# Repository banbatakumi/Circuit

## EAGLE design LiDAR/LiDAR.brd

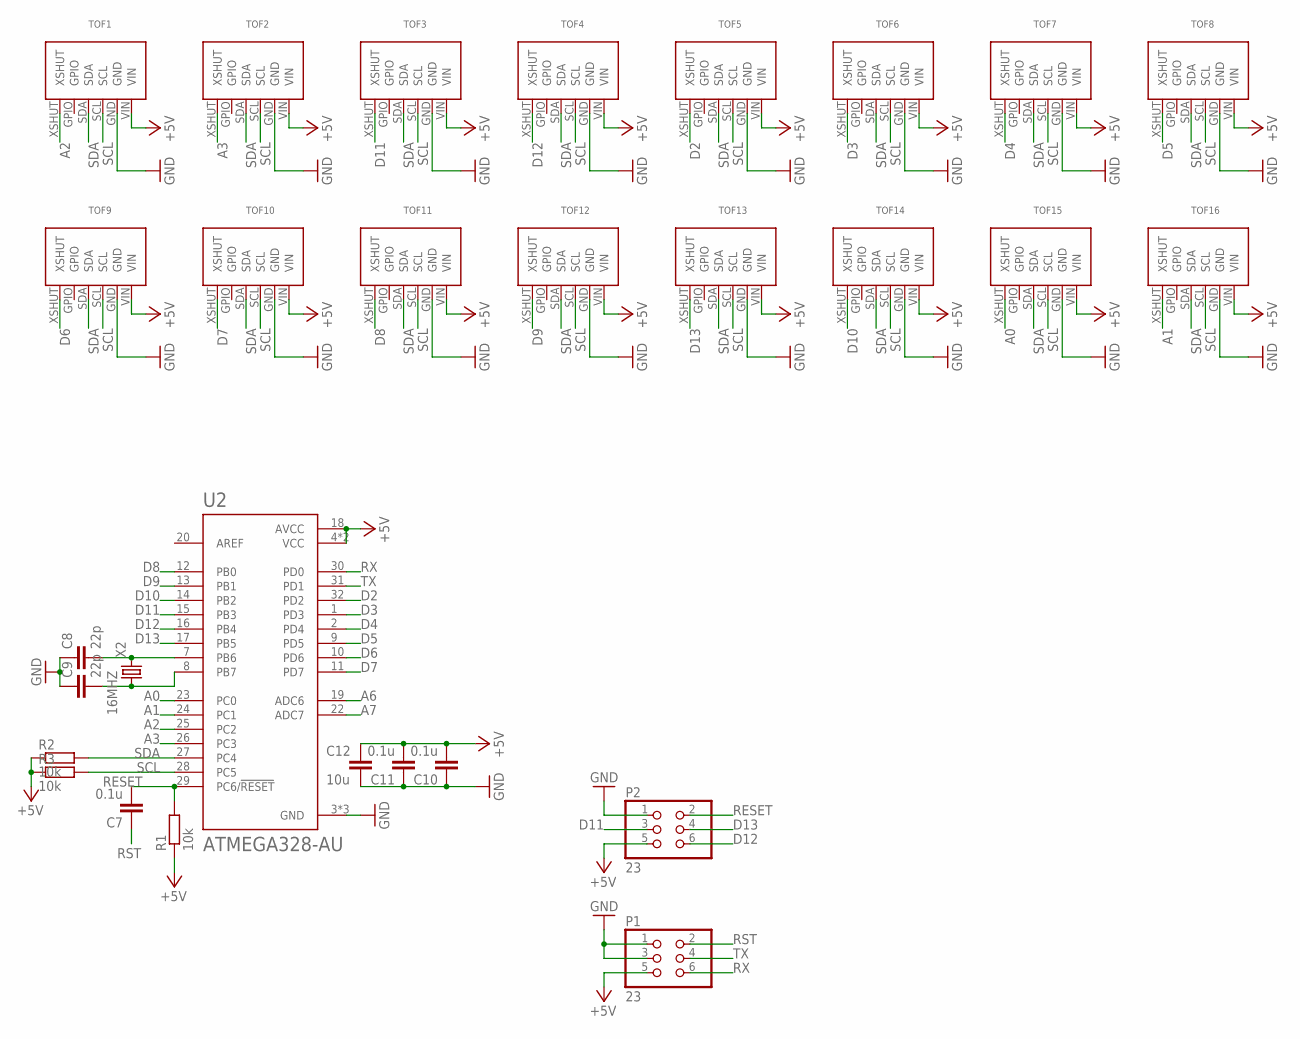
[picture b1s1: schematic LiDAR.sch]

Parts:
C7, C10, C11: 0.1u; C0603
C8, C9: 22p; C0603
C12: 10u; C0805
P1, P2: 23; 2*3
R1, R2, R3: 10k; 0204/7
TOF1, TOF2, TOF3, TOF4, TOF5, TOF6, TOF7, TOF8, TOF9, TOF10, TOF11, TOF12, TOF13, TOF14, TOF15, TOF16: VL53L0X
U2: ATMEGA328-AU; QFP80P900X900X120-32N
X2: 16MHZ

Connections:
+5V: C10.2, C11.2, C12.1, P1.5, P2.5, R1.1, R2.1, R3.1, TOF1.VIN, TOF2.VIN, TOF3.VIN, TOF4.VIN, TOF5.VIN, TOF6.VIN, TOF7.VIN, TOF8.VIN, TOF9.VIN, TOF10.VIN, TOF11.VIN, TOF12.VIN, TOF13.VIN, TOF14.VIN, TOF15.VIN, TOF16.VIN, U2.4 (VCC), U2.6 (VCC), U2.18 (AVCC)
A0: TOF15.XSHUT, U2.23 (PC0)
A1: TOF16.XSHUT, U2.24 (PC1)
A2: TOF1.XSHUT, U2.25 (PC2)
A3: TOF2.XSHUT, U2.26 (PC3)
A6: U2.19 (ADC6)
A7: U2.22 (ADC7)
D2: TOF5.XSHUT, U2.32 (PD2)
D3: TOF6.XSHUT, U2.1 (PD3)
D4: TOF7.XSHUT, U2.2 (PD4)
D5: TOF8.XSHUT, U2.9 (PD5)
D6: TOF9.XSHUT, U2.10 (PD6)
D7: TOF10.XSHUT, U2.11 (PD7)
D8: TOF11.XSHUT, U2.12 (PB0)
D9: TOF12.XSHUT, U2.13 (PB1)
D10: TOF14.XSHUT, U2.14 (PB2)
D11: P2.3, TOF3.XSHUT, U2.15 (PB3)
D12: P2.6, TOF4.XSHUT, U2.16 (PB4)
D13: P2.4, TOF13.XSHUT, U2.17 (PB5)
GND: C8.1, C9.1, C10.1, C11.1, C12.2, P1.1, P1.3, P2.1, TOF1.GND, TOF2.GND, TOF3.GND, TOF4.GND, TOF5.GND, TOF6.GND, TOF7.GND, TOF8.GND, TOF9.GND, TOF10.GND, TOF11.GND, TOF12.GND, TOF13.GND, TOF14.GND, TOF15.GND, TOF16.GND, U2.3 (GND), U2.5 (GND), U2.21 (GND)
unnamed: C8.2, U2.7 (PB6), X2.P$2 (2)
unnamed: C9.2, U2.8 (PB7), X2.P$1 (1)
RESET: C7.2, P2.2, R1.2, U2.29 (PC6/!RESET)
RST: C7.1, P1.2
RX: P1.6, U2.30 (PD0)
SCL: R3.2, TOF1.SCL, TOF2.SCL, TOF3.SCL, TOF4.SCL, TOF5.SCL, TOF6.SCL, TOF7.SCL, TOF8.SCL, TOF9.SCL, TOF10.SCL, TOF11.SCL, TOF12.SCL, TOF13.SCL, TOF14.SCL, TOF15.SCL, TOF16.SCL, U2.28 (PC5)
SDA: R2.2, TOF1.SDA, TOF2.SDA, TOF3.SDA, TOF4.SDA, TOF5.SDA, TOF6.SDA, TOF7.SDA, TOF8.SDA, TOF9.SDA, TOF10.SDA, TOF11.SDA, TOF12.SDA, TOF13.SDA, TOF14.SDA, TOF15.SDA, TOF16.SDA, U2.27 (PC4)
TX: P1.4, U2.31 (PD1)

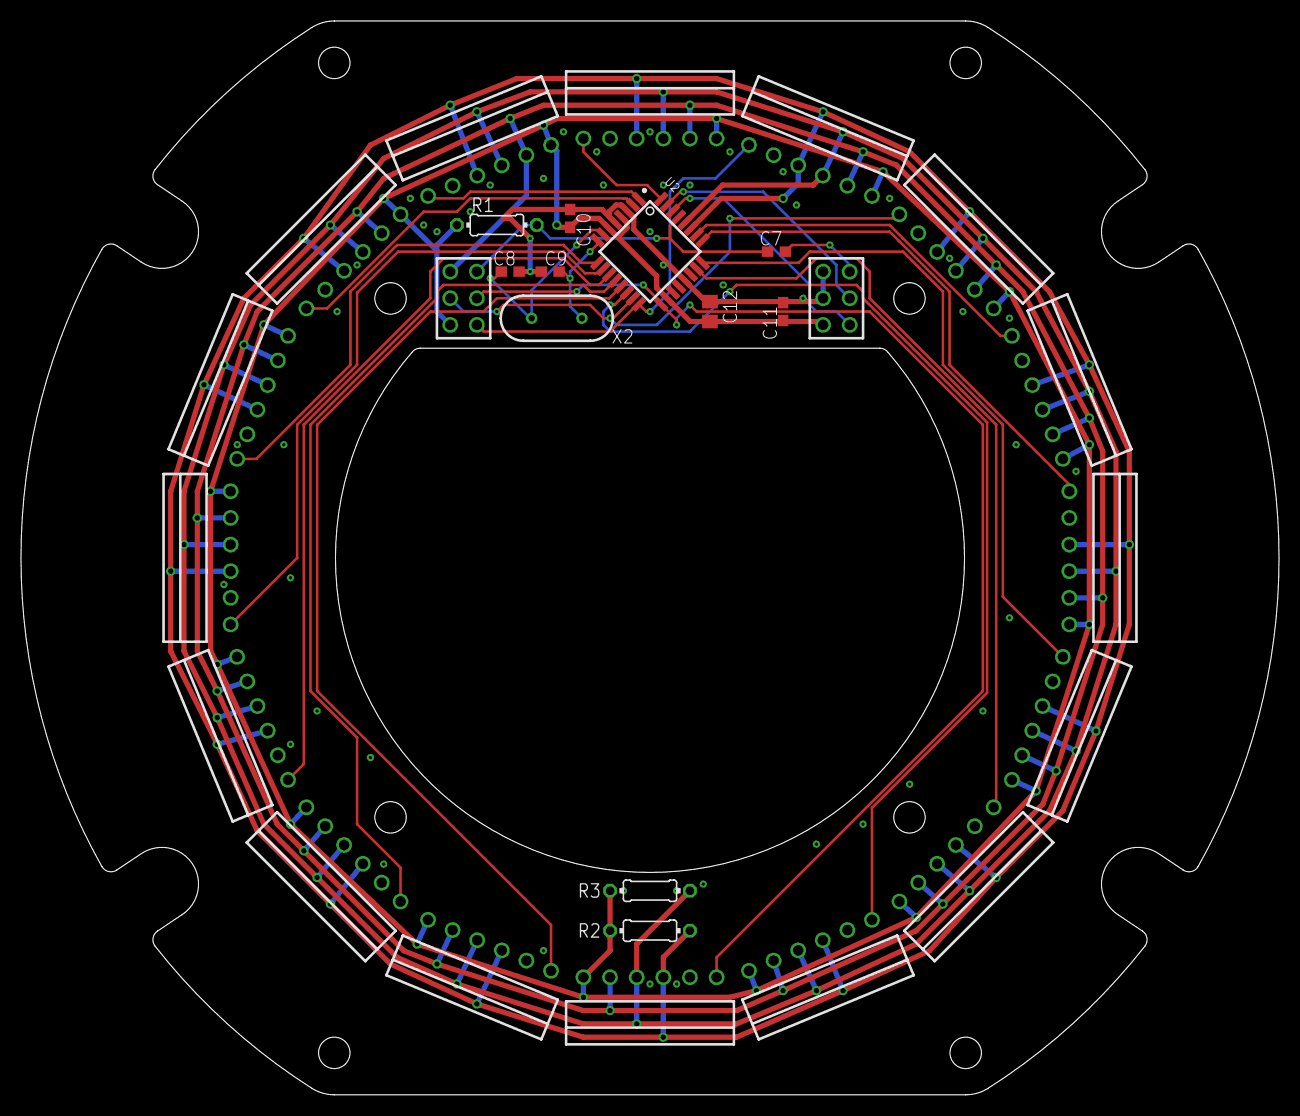
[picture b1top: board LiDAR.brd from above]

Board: 2 copper layers, 120.0 x 102.4 mm, 29 parts (0 on the bottom side), 26 nets.

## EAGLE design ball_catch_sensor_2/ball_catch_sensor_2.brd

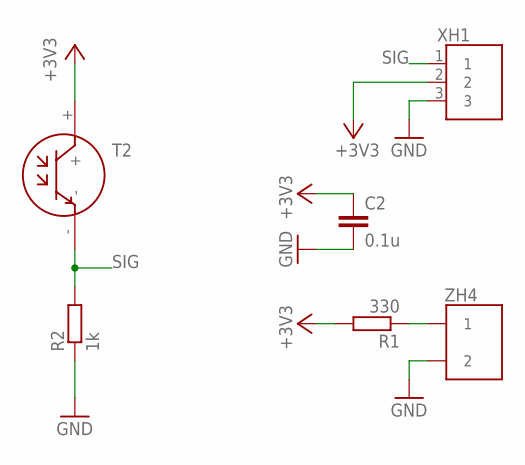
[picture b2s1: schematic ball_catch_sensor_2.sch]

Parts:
C2: 0.1u; C0603
R1: 330; 0207/10
R2: 1k; 0207/10
T2: NJL7302L-F3
XH1: S3B
ZH4: 2B

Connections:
+3V3: C2.1, R1.2, T2.+, XH1.2
GND: C2.2, R2.1, XH1.3, ZH4.2
unnamed: R1.1, ZH4.1
SIG: R2.2, T2.-, XH1.1

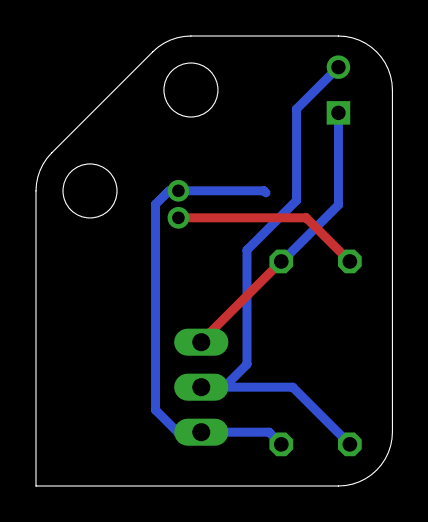
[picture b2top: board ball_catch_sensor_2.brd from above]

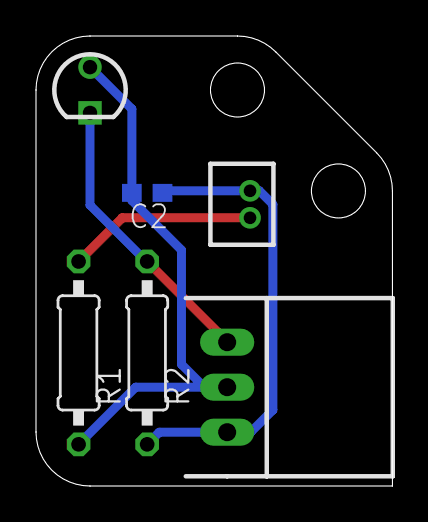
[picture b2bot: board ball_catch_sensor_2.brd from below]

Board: 2 copper layers, 19.8 x 25.0 mm, 6 parts (6 on the bottom side), 4 nets.

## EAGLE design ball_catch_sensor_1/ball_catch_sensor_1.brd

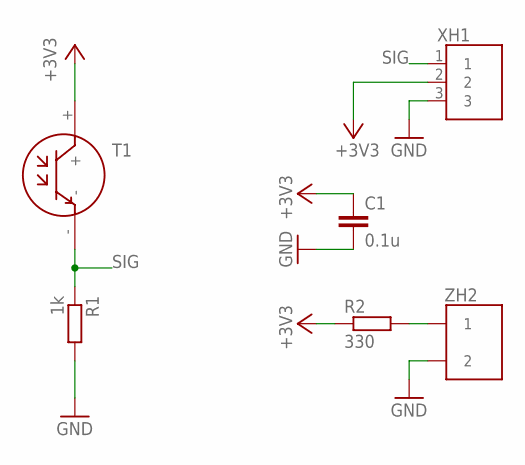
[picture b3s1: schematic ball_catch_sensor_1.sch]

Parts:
C1: 0.1u; C0603
R1: 1k; 0207/10
R2: 330; 0207/10
T1: NJL7302L-F3
XH1: S3B
ZH2: 2B

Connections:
+3V3: C1.1, R2.1, T1.+, XH1.2
GND: C1.2, R1.2, XH1.3, ZH2.2
unnamed: R2.2, ZH2.1
SIG: R1.1, T1.-, XH1.1

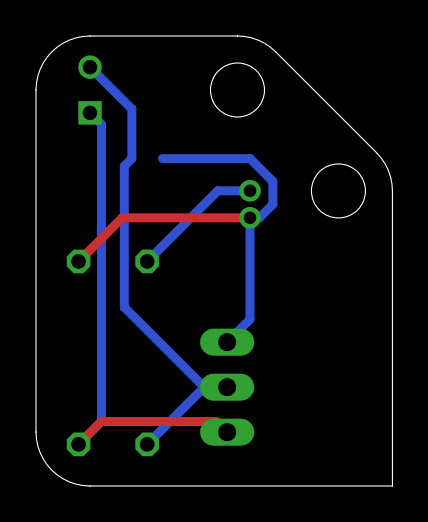
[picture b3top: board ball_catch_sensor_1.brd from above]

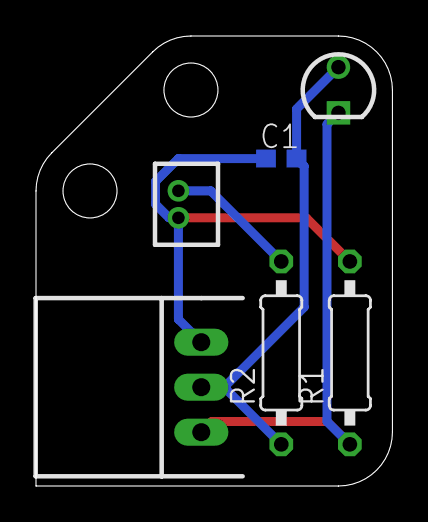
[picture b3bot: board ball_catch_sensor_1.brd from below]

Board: 2 copper layers, 19.8 x 25.0 mm, 6 parts (6 on the bottom side), 4 nets.

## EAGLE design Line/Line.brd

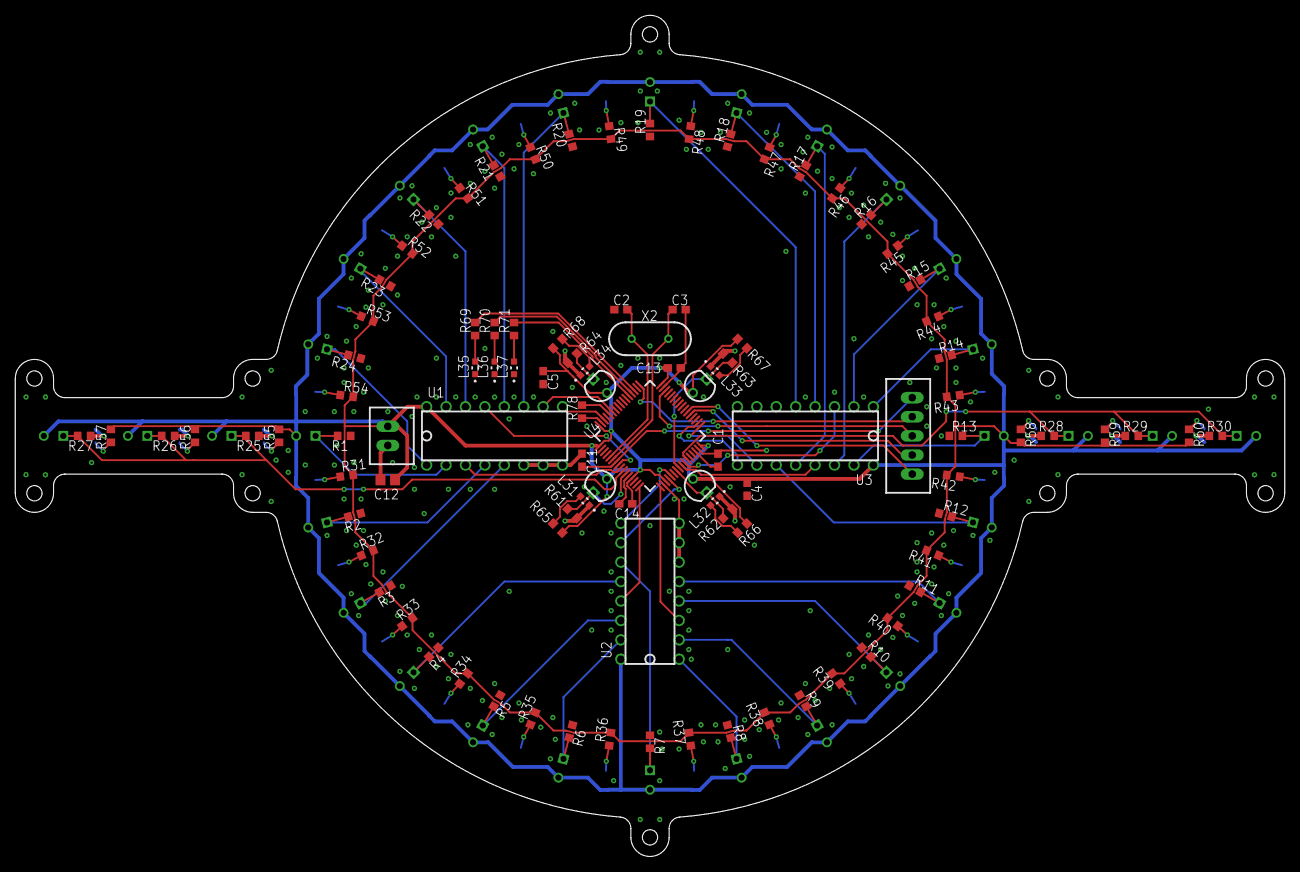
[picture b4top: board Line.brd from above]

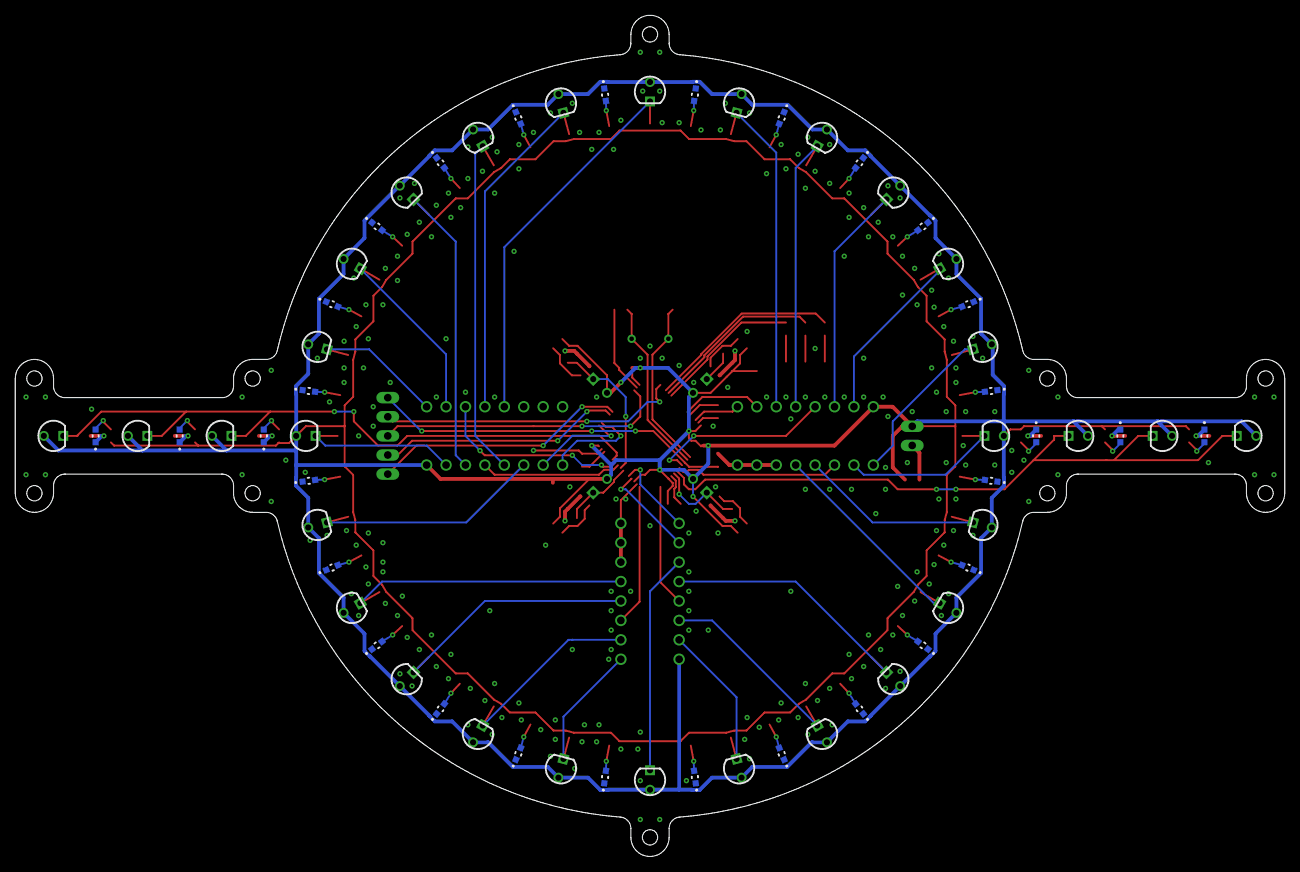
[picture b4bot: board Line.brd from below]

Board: 2 copper layers, 166.0 x 110.0 mm, 159 parts (60 on the bottom side), 93 nets.

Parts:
C1: 4.7u; C0603
C2, C3: 22p; C0603
C4, C5, C11, C13, C14: 0.1u; C0603
C12: 10u; C0805
L1, L2, L3, L4, L5, L6, L7, L8, L9, L10, L11, L12, L13, L14, L15, L16, L17, L18, L19, L20, L21, L22, L23, L24, L25, L26, L27, L28, L29, L30, L31, L32, L33, L34, L35, L36, L37: SML-E12P8WT86; LED_SML-LXFM0603SIC-TR
R1, R2, R3, R4, R5, R6, R7, R8, R9, R10, R11, R12, R13, R14, R15, R16, R17, R18, R19, R20, R21, R22, R23, R24, R25, R26, R27, R28, R29, R30, R61, R62, R63, R64: 1k; R0603
R31, R32, R33, R34, R35, R36, R37, R38, R39, R40, R41, R42, R43, R44, R45, R46, R47, R48, R49, R50, R51, R52, R53, R54, R55, R56, R57, R58, R59, R60, R65, R66, R67, R68: 47; R0603
R69, R70, R71: 150; R0603
R78: 10k; R0603
T1, T2, T3, T4, T5, T6, T7, T8, T9, T10, T11, T12, T13, T14, T15, T16, T17, T18, T19, T20, T21, T22, T23, T24, T25, T26, T27, T28, T29, T30, T31, T32, T33, T34: NJL7302L-F3
U1, U2, U3: TC4051BP
U4: STM32F446RET6; QFP50P1200X1200X160-64N
X2: 8MHZ; 16MHZ
XH1: 5B
XH2: 2B

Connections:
+3V3: C4.1, C5.1, C12.1, C13.1, C14.1, R31.2, R32.2, R33.2, R34.2, R35.2, R36.2, R37.2, R38.2, R39.2, R40.2, R41.2, R42.2, R43.2, R44.2, R45.2, R46.2, R47.2, R48.2, R49.2, R50.2, R51.2, R52.2, R53.2, R54.2, R55.2, R56.2, R57.2, R58.2, R59.2, R60.2, R65.2, R66.2, R67.2, R68.2, T1.+, T2.+, T3.+, T4.+, T5.+, T6.+, T7.+, T8.+, T9.+, T10.+, T11.+, T12.+, T13.+, T14.+, T15.+, T16.+, T17.+, T18.+, T19.+, T20.+, T21.+, T22.+, T23.+, T24.+, T25.+, T26.+, T27.+, T28.+, T29.+, T30.+, T31.+, T32.+, T33.+, T34.+, U1.VDD, U2.VDD, U3.VDD, U4.1, U4.13, U4.19, U4.32, U4.48, U4.64, XH2.P$1
GND: C1.2, C2.2, C3.2, C4.2, C5.2, C11.2, C12.2, C13.2, C14.2, L1.C, L2.C, L3.C, L4.C, L5.C, L6.C, L7.C, L8.C, L9.C, L10.C, L11.C, L12.C, L13.C, L14.C, L15.C, L16.C, L17.C, L18.C, L19.C, L20.C, L21.C, L22.C, L23.C, L24.C, L25.C, L26.C, L27.C, L28.C, L29.C, L30.C, L31.C, L32.C, L33.C, L34.C, L35.C, L36.C, L37.C, R1.1, R2.1, R3.1, R4.1, R5.1, R6.1, R7.1, R8.1, R9.1, R10.1, R11.1, R12.1, R13.1, R14.1, R15.1, R16.1, R17.1, R18.1, R19.1, R20.1, R21.1, R22.1, R23.1, R24.1, R25.1, R26.1, R27.1, R28.1, R29.1, R30.1, R61.1, R62.1, R63.1, R64.1, R78.1, U1.INH, U1.VEE, U1.VSS, U2.INH, U2.VEE, U2.VSS, U3.INH, U3.VEE, U3.VSS, U4.12, U4.18, U4.31, U4.47, U4.63, XH2.P$2
LED1: R69.2, U4.51
LED2: R70.2, U4.52
LED3: R71.2, U4.53
LINE_RX_LV: U4.38, XH1.1
LINE_TX_LV: U4.37, XH1.2
unnamed: L1.A, R31.1
unnamed: L2.A, R32.1
unnamed: L3.A, R33.1
unnamed: L4.A, R34.1
unnamed: L5.A, R35.1
unnamed: L6.A, R36.1
unnamed: L7.A, R37.1
unnamed: L8.A, R38.1
unnamed: L9.A, R39.1
unnamed: L10.A, R40.1
unnamed: L11.A, R41.1
unnamed: L12.A, R42.1
unnamed: L13.A, R43.1
unnamed: L14.A, R44.1
unnamed: L15.A, R45.1
unnamed: L16.A, R46.1
unnamed: L17.A, R47.1
unnamed: L18.A, R48.1
unnamed: L19.A, R49.1
unnamed: L20.A, R50.1
unnamed: L21.A, R51.1
unnamed: L22.A, R52.1
unnamed: L23.A, R53.1
unnamed: L24.A, R54.1
unnamed: L25.A, R55.1
unnamed: L26.A, R56.1
unnamed: L27.A, R57.1
unnamed: L28.A, R58.1
unnamed: L29.A, R59.1
unnamed: L30.A, R60.1
unnamed: L31.A, R65.1
unnamed: L32.A, R66.1
unnamed: L33.A, R67.1
unnamed: L34.A, R68.1
unnamed: L35.A, R69.1
unnamed: L36.A, R70.1
unnamed: L37.A, R71.1
unnamed: C1.1, U4.30
unnamed: R78.2, U4.60
unnamed: C2.1, U4.5, X2.P$2
unnamed: C3.1, U4.6, X2.P$1
PA_13: U4.46, XH1.3
PA_14: U4.49, XH1.4
RST: C11.1, U4.7, XH1.5
S1: R1.2, T1.-, U1.2Y
S2: R2.2, T2.-, U1.3Y
S3: R3.2, T3.-, U1.1Y
S4: R4.2, T4.-, U2.0X
S5: R5.2, T5.-, U2.1X
S6: R6.2, T6.-, U2.2X
S7: R7.2, T7.-, U2.3X
S8: R8.2, T8.-, U2.0Y
S9: R9.2, T9.-, U2.2Y
S10: R10.2, T10.-, U2.3Y
S11: R11.2, T11.-, U2.1Y
S12: R12.2, T12.-, U3.3X
S13: R13.2, T13.-, U3.2X
S14: R14.2, T14.-, U3.0Y
S15: R15.2, T15.-, U3.2Y
S16: R16.2, T16.-, U3.1X
S17: R17.2, T17.-, U3.0X
S18: R18.2, T18.-, U3.3Y
S19: R19.2, T19.-, U3.1Y
S20: R20.2, T20.-, U1.3X
S21: R21.2, T21.-, U1.0X
S22: R22.2, T22.-, U1.1X
S23: R23.2, T23.-, U1.2X
S24: R24.2, T24.-, U1.0Y
S25: R25.2, R26.2, R27.2, T25.-, T26.-, T27.-, U4.10
S26: R28.2, R29.2, R30.2, T28.-, T29.-, T30.-, U4.27
S27: R61.2, T31.-, U4.11
S28: R62.2, T32.-, U4.23
S29: R63.2, T33.-, U4.24
S30: R64.2, T34.-
U1A: U1.A, U4.59
U1B: U1.B, U4.62
U1X: U1.X-COM, U4.8
U1Y: U1.Y-COM, U4.9
U2A: U2.A, U4.20
U2B: U2.B, U4.21
U2X: U2.X-COM, U4.16
U2Y: U2.Y-COM, U4.17
U3A: U3.A, U4.33
U3B: U3.B, U4.34
U3X: U3.X-COM, U4.25
U3Y: U3.Y-COM, U4.26

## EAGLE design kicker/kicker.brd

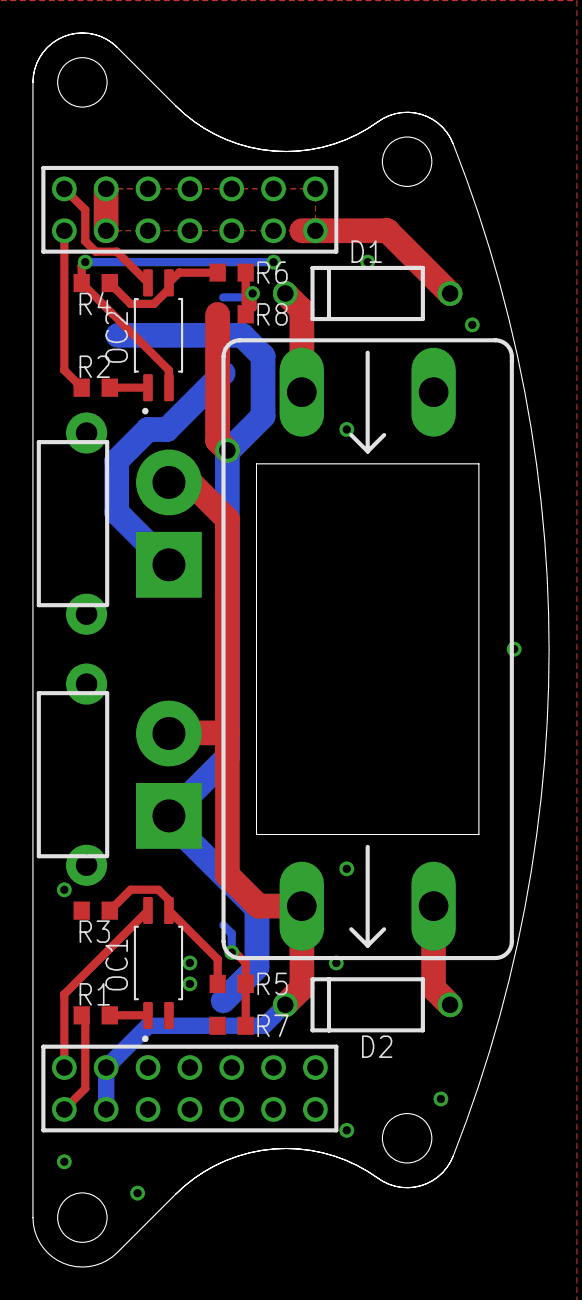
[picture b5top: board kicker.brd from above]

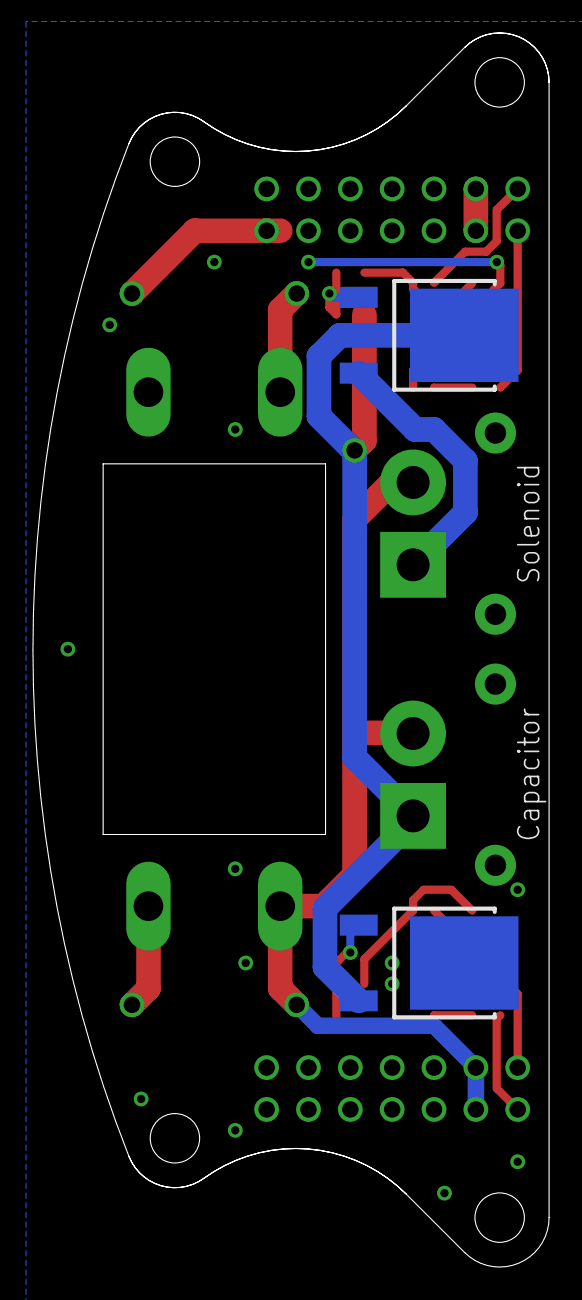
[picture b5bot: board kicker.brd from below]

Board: 2 copper layers, 31.3 x 74.9 mm, 19 parts (2 on the bottom side), 15 nets.

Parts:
D1, D2: UF2010
OC1, OC2: TL293(GB); SOIC127P700X230-4N
Q1, Q2: NP52N06SLG; TO230P1040X230-3N
R1, R2, R5, R6: 100; R0603
R3, R4: 200; R0603
R7, R8: 10k; R0603
U$1: MT3608
U$2, U$3: 27; 2*7
XT1, XT2: XT30PW-F

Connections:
40V: D2.C, U$1.VOUT+, U$2.11, U$2.12, XT1.+, XT2.+
+5V: OC1.COL, OC2.COL, U$2.13, U$3.13
GND: D2.A, OC1.C, OC2.C, Q1.D, R3.1, R4.2, R7.1, U$1.VIN-, U$1.VOUT-, U$2.1, U$2.2, U$2.3, U$2.4, U$2.5, U$2.6, U$2.7, U$2.8, U$2.9, U$2.10
unnamed: D1.C, U$1.VIN+
unnamed: Q1.S, Q2.D, R8.1, XT1.-
unnamed: OC1.EMI, R3.2, R5.2
unnamed: Q2.S, XT2.-
unnamed: OC1.A, R1.1
unnamed: OC2.A, R2.2
unnamed: OC2.EMI, R4.1, R6.2
unnamed: Q1.G, R5.1, R7.2
unnamed: Q2.G, R6.1, R8.2
SIG1: R1.2, U$2.14
SIG2: R2.1, U$3.14
VCC: D1.A, U$3.1, U$3.2, U$3.3, U$3.4, U$3.5, U$3.6, U$3.7, U$3.8, U$3.9, U$3.10, U$3.11, U$3.12

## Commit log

2023-08-16 Create dribbler
2023-08-16 add dribbler file
2023-08-16 Create cam
2023-08-16 add cam files
2023-08-16 Create ui
2023-08-16 add ui files
2023-08-16 Add dribbler files
2023-08-16 Add kicker files
2023-08-16 Add main_bottom files
2023-08-16 Add main_top files
2023-08-16 Add MD files
2023-08-16 Add supply files
2023-08-16 Add line files
2023-08-16 Add ball_catch_sensor_1 files
2023-08-16 Add ball_catch_sensor_2 files
2023-08-16 Add lidar files
2024-06-29 Add files via upload
    add_new_ball_catch
2024-06-29 Add files via upload
    add_cam_new
2024-06-29 Add files via upload
    add_ir
2024-06-29 Add files via upload
    add_kicker_v3
